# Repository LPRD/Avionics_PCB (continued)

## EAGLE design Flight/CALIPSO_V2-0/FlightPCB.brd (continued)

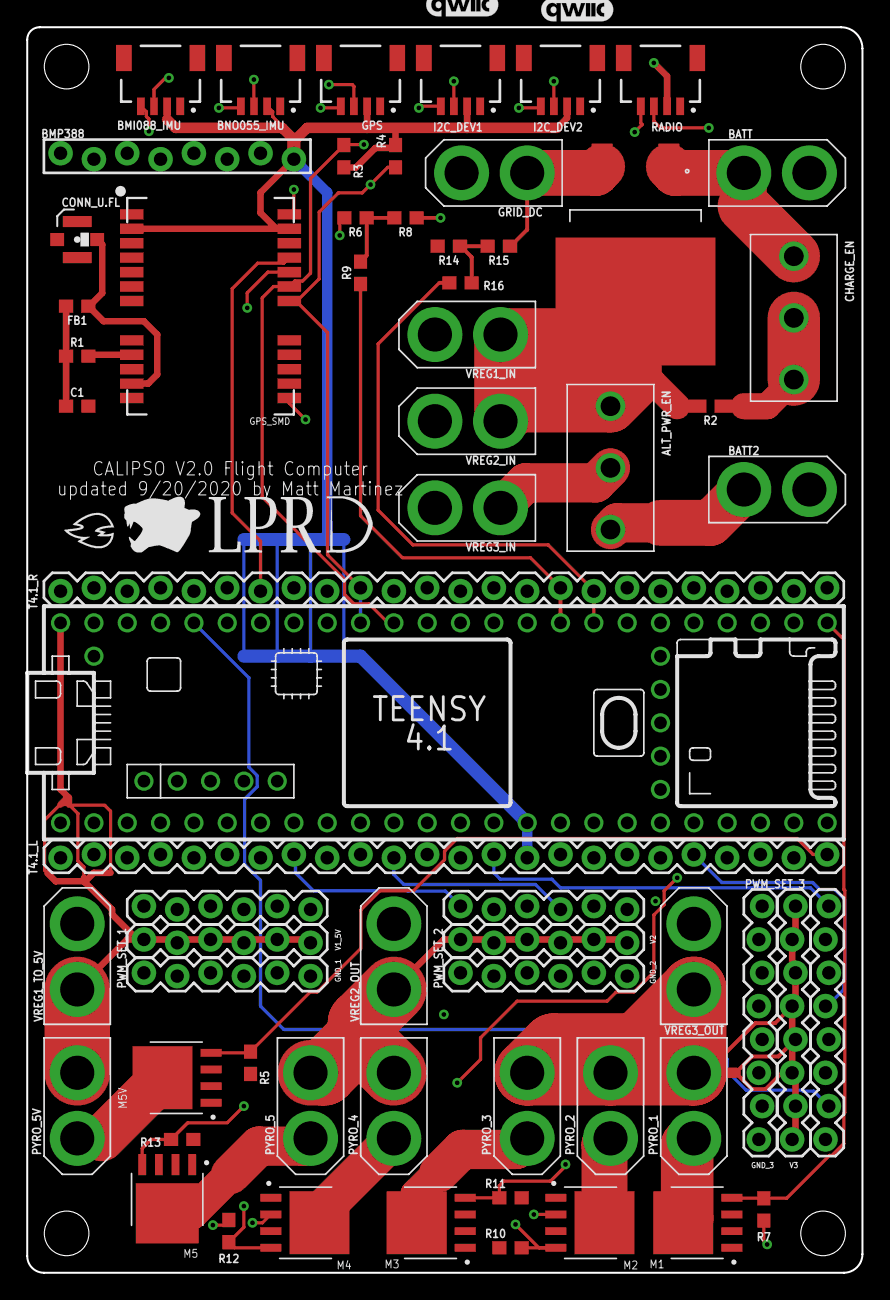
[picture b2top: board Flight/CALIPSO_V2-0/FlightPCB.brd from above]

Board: 4 copper layers, 63.6 x 94.9 mm, 65 parts (0 on the bottom side), 65 nets.

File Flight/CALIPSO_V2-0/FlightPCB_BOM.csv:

Part,Value,Device,Package,Description,PROD_ID,SF_ID,VALUE
ALT_PWR_EN,B2-Off-B1,CONN_03_SLIDE_SWITCH_EG5137,1X03_SLIDE_SWITCH_EG5137,Multi connection point. Often used as Generic Header-pin footprint for 0.1 inch spaced/style header connections,,,
BATT,XT-30,CONN_02_XT-30_CONNECTOR1X02_XT-30,1X02_BIG_XT-30,Multi connection point. Often used as Generic Header-pin footprint for 0.1 inch spaced/style header connections,,,
BATT2,XT-30,CONN_02_XT-30_CONNECTOR1X02_XT-30,1X02_BIG_XT-30,Multi connection point. Often used as Generic Header-pin footprint for 0.1 inch spaced/style header connections,,,
BMI088_IMU,QWIIC_RIGHT_ANGLE,QWIIC_CONNECTORJS-1MM,JST04_1MM_RA,SparkFun I2C Standard Qwiic Connector,CONN-13694,,QWIIC_RIGHT_ANGLE
BMP388,Pressure Sensor,CONN_08_BMP388_MODIFIEDFEMALE_LOCK,1X08_FEMALE_LOCK,Multi connection point. Often used as Generic Header-pin footprint for 0.1 inch spaced/style header connections,CONN-09233,PRT-09279,
BNO055_IMU,QWIIC_RIGHT_ANGLE,QWIIC_CONNECTORJS-1MM,JST04_1MM_RA,SparkFun I2C Standard Qwiic Connector,CONN-13694,,QWIIC_RIGHT_ANGLE
C1,47pF,47PF-0603-50V-5%,603,47pF ceramic capacitors,CAP-08913,,47pF
CHARGE_EN,Off-Off-Chg,CONN_03_SLIDE_SWITCH_EG5137,1X03_SLIDE_SWITCH_EG5137,Multi connection point. Often used as Generic Header-pin footprint for 0.1 inch spaced/style header connections,,,
CONN_U.FL,U.FL,U.FL2PIN,U.FL,SMD Antenna Connector - U.FL,CONN-09193,WRL-09144,U.FL
FB1,30Ω/1.8A,FERRITE_BEAD-0603,603,Ferrite Bead (blocks,,,
GND_1,6pin,CONN_06LOCK,1X06_LOCK,Multi connection point. Often used as Generic Header-pin footprint for 0.1 inch spaced/style header connections,,,
GND_2,6pin,CONN_06LOCK,1X06_LOCK,Multi connection point. Often used as Generic Header-pin footprint for 0.1 inch spaced/style header connections,,,
GND_3,8pin,CONN_08LOCK,1X08_LOCK,Multi connection point. Often used as Generic Header-pin footprint for 0.1 inch spaced/style header connections,,,
GPS,QWIIC_RIGHT_ANGLE,QWIIC_CONNECTORJS-1MM,JST04_1MM_RA,SparkFun I2C Standard Qwiic Connector,CONN-13694,,QWIIC_RIGHT_ANGLE
GPS_SMD,U-BLOX_NEO-M9N,U-BLOX_NEO-M9N,NEO-M9N/M8T/M8U,u-blox NEO-M9N GPS Module,IC-14651,,
GRID_DC,XT-30,CONN_02_XT-30_CONNECTOR1X02_XT-30,1X02_BIG_XT-30,Multi connection point. Often used as Generic Header-pin footprint for 0.1 inch spaced/style header connections,,,
I2C_DEV1,QWIIC_RIGHT_ANGLE,QWIIC_CONNECTORJS-1MM,JST04_1MM_RA,SparkFun I2C Standard Qwiic Connector,CONN-13694,,QWIIC_RIGHT_ANGLE
I2C_DEV2,QWIIC_RIGHT_ANGLE,QWIIC_CONNECTORJS-1MM,JST04_1MM_RA,SparkFun I2C Standard Qwiic Connector,CONN-13694,,QWIIC_RIGHT_ANGLE
LOGO1,QWIIC_LOGO_4MM,QWIIC_LOGO_4MM,QWIIC_4MM,Qwiic Logos for placement on schematic and PCB. The 5.5mm silk logo is best for placing next to Qwiic connector.,,,
LOGO2,QWIIC_LOGO_4MM,QWIIC_LOGO_4MM,QWIIC_4MM,Qwiic Logos for placement on schematic and PCB. The 5.5mm silk logo is best for placing next to Qwiic connector.,,,
M1,MOSFET_60V_22A,"BUK9Y43-60E,115",SOT-669-4,,,,
M2,MOSFET_60V_22A,"BUK9Y43-60E,115",SOT-669-4,,,,
M3,MOSFET_60V_22A,"BUK9Y43-60E,115",SOT-669-4,,,,
M4,MOSFET_60V_22A,"BUK9Y43-60E,115",SOT-669-4,,,,
M5,MOSFET_60V_22A,"BUK9Y43-60E,115",SOT-669-4,,,,
M5V,MOSFET_60V_22A,"BUK9Y43-60E,115",SOT-669-4,,,,
PWM_SET_1,6pin,CONN_06LOCK,1X06_LOCK,Multi connection point. Often used as Generic Header-pin footprint for 0.1 inch spaced/style header connections,,,
PWM_SET_2,6pin,CONN_06LOCK,1X06_LOCK,Multi connection point. Often used as Generic Header-pin footprint for 0.1 inch spaced/style header connections,,,
PWM_SET_3,8pin,CONN_08LOCK,1X08_LOCK,Multi connection point. Often used as Generic Header-pin footprint for 0.1 inch spaced/style header connections,,,
PWR_SWITCHER,STPS30170CG-TR_2_DIODES,STPS30170CG-TR,TO-263-3,,,,
PYRO_1,XT-30,CONN_02_XT-30_CONNECTOR1X02_XT-30,1X02_BIG_XT-30,Multi connection point. Often used as Generic Header-pin footprint for 0.1 inch spaced/style header connections,,,
PYRO_2,XT-30,CONN_02_XT-30_CONNECTOR1X02_XT-30,1X02_BIG_XT-30,Multi connection point. Often used as Generic Header-pin footprint for 0.1 inch spaced/style header connections,,,
PYRO_3,XT-30,CONN_02_XT-30_CONNECTOR1X02_XT-30,1X02_BIG_XT-30,Multi connection point. Often used as Generic Header-pin footprint for 0.1 inch spaced/style header connections,,,
PYRO_4,XT-30,CONN_02_XT-30_CONNECTOR1X02_XT-30,1X02_BIG_XT-30,Multi connection point. Often used as Generic Header-pin footprint for 0.1 inch spaced/style header connections,,,
PYRO_5,XT-30,CONN_02_XT-30_CONNECTOR1X02_XT-30,1X02_BIG_XT-30,Multi connection point. Often used as Generic Header-pin footprint for 0.1 inch spaced/style header connections,,,
PYRO_5V,XT-30,CONN_02_XT-30_CONNECTOR1X02_XT-30,1X02_BIG_XT-30,Multi connection point. Often used as Generic Header-pin footprint for 0.1 inch spaced/style header connections,,,
R1,10,10OHM-0603-1/10W-1%,603,10Ω resistor,RES-12581,,10
R2,1k,1KOHM-0603-1/10W-1%,603,1kΩ resistor,RES-07856,,1k
R3,4.7k,4.7KOHM-0603-1/10W-1%,603,4.7kΩ resistor,RES-07857,,4.7k
R4,4.7k,4.7KOHM-0603-1/10W-1%,603,4.7kΩ resistor,RES-07857,,4.7k
R5,10k,10KOHM-0603-1/10W-1%,603,10kΩ resistor,RES-00824,,10k
R6,1k,1KOHM-0603-1/10W-1%,603,1kΩ resistor,RES-07856,,1k
R7,10k,10KOHM-0603-1/10W-1%,603,10kΩ resistor,RES-00824,,10k
R8,20k,20KOHM-0603-1/10W-1%,603,20kΩ resistor,RES-09383,,20k
R9,20k,20KOHM-0603-1/10W-1%,603,20kΩ resistor,RES-09383,,20k
R10,10k,10KOHM-0603-1/10W-1%,603,10kΩ resistor,RES-00824,,10k
R11,10k,10KOHM-0603-1/10W-1%,603,10kΩ resistor,RES-00824,,10k
R12,10k,10KOHM-0603-1/10W-1%,603,10kΩ resistor,RES-00824,,10k
R13,10k,10KOHM-0603-1/10W-1%,603,10kΩ resistor,RES-00824,,10k
R14,1k,1KOHM-0603-1/10W-1%,603,1kΩ resistor,RES-07856,,1k
R15,20k,20KOHM-0603-1/10W-1%,603,20kΩ resistor,RES-09383,,20k
R16,20k,20KOHM-0603-1/10W-1%,603,20kΩ resistor,RES-09383,,20k
RADIO,QWIIC_RIGHT_ANGLE,QWIIC_CONNECTOR_SERIAL_RADIO_MODIFIEDJS-1MM,JST04_1MM_RA,SparkFun I2C Standard Qwiic Connector,CONN-13694,,QWIIC_RIGHT_ANGLE
T4.1_L,24p,CONN_24LOCK,1X24_LOCK,Multi connection point. Often used as Generic Header-pin footprint for 0.1 inch spaced/style header connections,,,
T4.1_R,24p,CONN_24LOCK,1X24_LOCK,Multi connection point. Often used as Generic Header-pin footprint for 0.1 inch spaced/style header connections,,,
TEENSY_4.1,TEENSY_4.1,TEENSY_4.1,TEENSY_4.1,,,,
V1_5V,6 pin,CONN_06LOCK,1X06_LOCK,Multi connection point. Often used as Generic Header-pin footprint for 0.1 inch spaced/style header connections,,,
V2,6 pin,CONN_06LOCK,1X06_LOCK,Multi connection point. Often used as Generic Header-pin footprint for 0.1 inch spaced/style header connections,,,
V3,8 pin,CONN_08LOCK,1X08_LOCK,Multi connection point. Often used as Generic Header-pin footprint for 0.1 inch spaced/style header connections,,,
VREG1_IN,XT-30,CONN_02_XT-30_CONNECTOR1X02_XT-30,1X02_BIG_XT-30,Multi connection point. Often used as Generic Header-pin footprint for 0.1 inch spaced/style header connections,,,
VREG1_TO_5V,XT-30,CONN_02_XT-30_CONNECTOR1X02_XT-30,1X02_BIG_XT-30,Multi connection point. Often used as Generic Header-pin footprint for 0.1 inch spaced/style header connections,,,
VREG2_IN,XT-30,CONN_02_XT-30_CONNECTOR1X02_XT-30,1X02_BIG_XT-30,Multi connection point. Often used as Generic Header-pin footprint for 0.1 inch spaced/style header connections,,,
VREG2_OUT,XT-30,CONN_02_XT-30_CONNECTOR1X02_XT-30,1X02_BIG_XT-30,Multi connection point. Often used as Generic Header-pin footprint for 0.1 inch spaced/style header connections,,,
VREG3_IN,XT-30,CONN_02_XT-30_CONNECTOR1X02_XT-30,1X02_BIG_XT-30,Multi connection point. Often used as Generic Header-pin footprint for 0.1 inch spaced/style header connections,,,
VREG3_OUT,XT-30,CONN_02_XT-30_CONNECTOR1X02_XT-30,1X02_BIG_XT-30,Multi connection point. Often used as Generic Header-pin footprint for 0.1 inch spaced/style header connections,,,

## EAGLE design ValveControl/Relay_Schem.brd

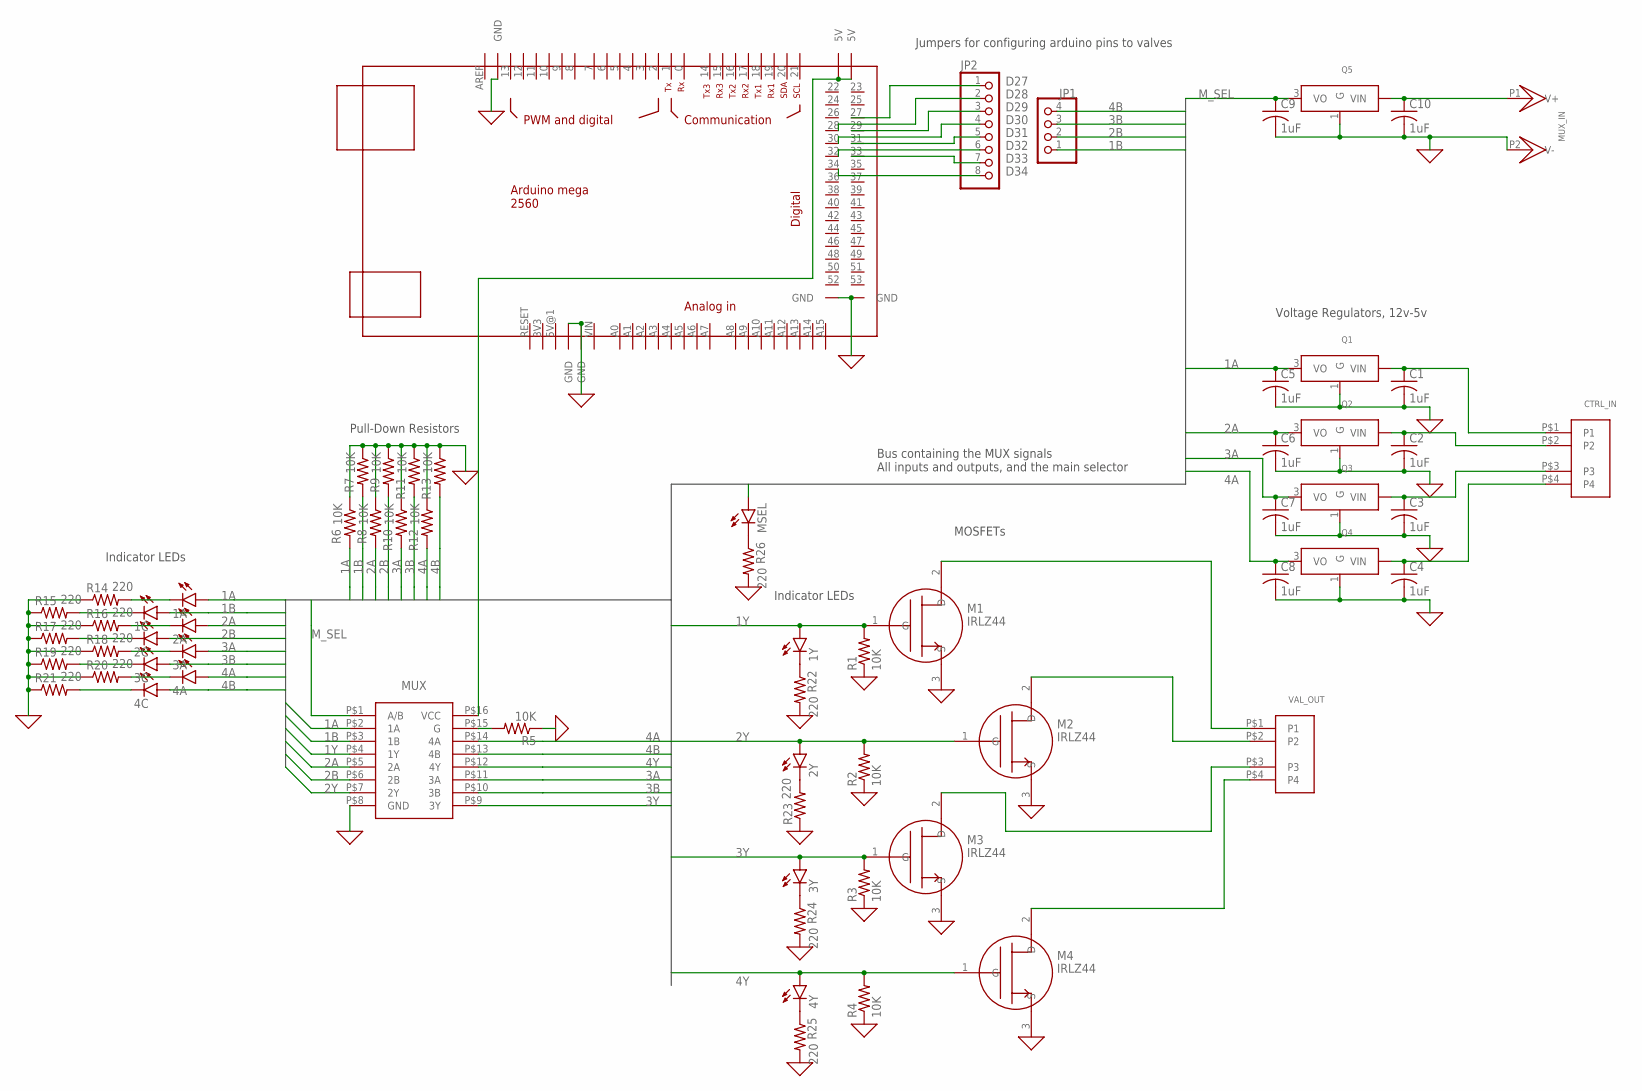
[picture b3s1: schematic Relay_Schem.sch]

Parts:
1A, 1C, 1Y, 2A, 2C, 2Y, 3A, 3C, 3Y, 4A, 4C, 4Y: LED3MM
C1, C2, C3, C4, C5, C6, C7, C8, C9, C10: 1uF; C025-024X044
CTRL_IN: JST_CONNECTOR; B4B-XH-A(LF)(SN)
JP1: PINHD-1X4; 1X04
JP2: PINHD-1X8; 1X08
M1, M2, M3, M4: IRLZ44; TO220V
MSEL: LED3MM
MUX: MULTIPLEXER; SN74HC157
MUX_IN: COAX_POW_2.1MM; PJ-102A
Q1, Q2, Q3, Q4, Q5: LINEAR_REGULATOR; LINREG_FP
R1, R2, R3, R4, R5, R6, R7, R8, R9, R10, R11, R12, R13: 10K; 0204/7
R14, R15, R16, R17, R18, R19, R20, R21, R22, R23, R24, R25, R26: 220; 0204/7
U$2: MEGA_DEVICE; MEGAOUTLINE
VAL_OUT: JST_CONNECTOR; B4B-XH-A(LF)(SN)

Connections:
0: C1.2, C2.2, C3.2, C4.2, C5.2, C6.2, C7.2, C8.2, C9.2, C10.2, M1.3 (S), M2.3 (S), M3.3 (S), M4.3 (S), MUX.P$8 (GND), MUX_IN.P2 (V-), Q1.1 (G), Q2.1 (G), Q3.1 (G), Q4.1 (G), Q5.1 (G), R1.1, R2.1, R3.1, R4.1, R5.1, R6.1, R7.1, R8.1, R9.1, R10.1, R11.1, R12.1, R13.1, R14.1, R15.1, R16.1, R17.1, R18.1, R19.1, R20.1, R21.1, R22.2, R23.1, R24.2, R25.2, R26.2, U$2.GND@1 (GND), U$2.GND@2 (GND), U$2.GND@3 (GND), U$2.GND@4 (GND), U$2.GND@5 (GND)
1A: 1A.A, C5.1, MUX.P$2 (1A), Q1.3 (VO), R6.2
1B: 1C.A, JP1.1, MUX.P$3 (1B), R7.2
1Y: 1Y.A, M1.1 (G), MUX.P$4 (1Y), R1.2
2A: 2A.A, C6.1, MUX.P$5 (2A), Q2.3 (VO), R8.2
2B: 2C.A, JP1.2, MUX.P$6 (2B), R9.2
2Y: 2Y.A, M2.1 (G), MUX.P$7 (2Y), R2.2
3A: 3A.A, C7.1, MUX.P$11 (3A), Q3.3 (VO), R10.2
3B: 3C.A, JP1.3, MUX.P$10 (3B), R11.2
3Y: 3Y.A, M3.1 (G), MUX.P$9 (3Y), R3.2
4A: 4A.A, C8.1, MUX.P$14 (4A), Q4.3 (VO), R12.2
4B: 4C.A, JP1.4, MUX.P$13 (4B), R13.2
4Y: 4Y.A, M4.1 (G), MUX.P$12 (4Y), R4.2
D27: JP2.1, U$2.27
D28: JP2.2, U$2.28
D29: JP2.3, U$2.29
D30: JP2.4, U$2.30
D31: JP2.5, U$2.31
D32: JP2.6, U$2.32
D33: JP2.7, U$2.33
D34: JP2.8, U$2.34
M_SEL: C9.1, MSEL.A, MUX.P$1 (A/B), Q5.3 (VO)
unnamed: C1.1, CTRL_IN.P$1 (P1), Q1.2 (VIN)
unnamed: C2.1, CTRL_IN.P$2 (P2), Q2.2 (VIN)
unnamed: M1.2 (D), VAL_OUT.P$1 (P1)
unnamed: C3.1, CTRL_IN.P$3 (P3), Q3.2 (VIN)
unnamed: M2.2 (D), VAL_OUT.P$2 (P2)
unnamed: MUX.P$16 (VCC), U$2.5V@2 (5V), U$2.5V@3 (5V)
unnamed: MSEL.K (C), R26.1
unnamed: M3.2 (D), VAL_OUT.P$3 (P3)
unnamed: M4.2 (D), VAL_OUT.P$4 (P4)
unnamed: MUX.P$15 (G), R5.2
unnamed: 1Y.K (C), R22.1
unnamed: C4.1, CTRL_IN.P$4 (P4), Q4.2 (VIN)
unnamed: 4A.K (C), R20.2
unnamed: 3A.K (C), R18.2
unnamed: 2A.K (C), R16.2
unnamed: 1A.K (C), R14.2
unnamed: 1C.K (C), R15.2
unnamed: 2C.K (C), R17.2
unnamed: 3C.K (C), R19.2
unnamed: 4C.K (C), R21.2
unnamed: 2Y.K (C), R23.2
unnamed: 3Y.K (C), R24.1
unnamed: 4Y.K (C), R25.1
unnamed: C10.1, MUX_IN.P1 (V+), Q5.2 (VIN)

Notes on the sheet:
MOSFETs
Indicator LEDs
Pull-Down Resistors
Voltage Regulators, 12v-5v
Bus containing the MUX signals All inputs and outputs, and the main selector
Jumpers for configuring arduino pins to valves

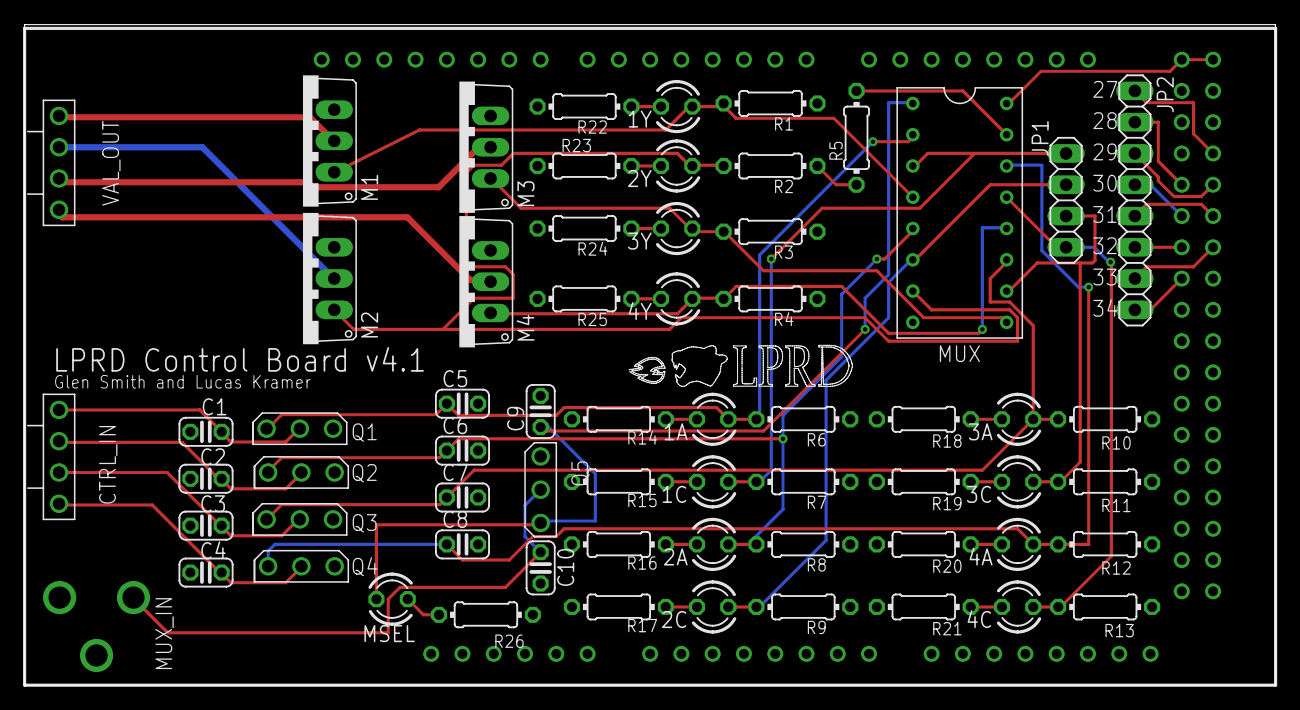
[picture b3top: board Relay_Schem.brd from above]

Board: 2 copper layers, 101.6 x 53.6 mm, 65 parts (0 on the bottom side), 46 nets.

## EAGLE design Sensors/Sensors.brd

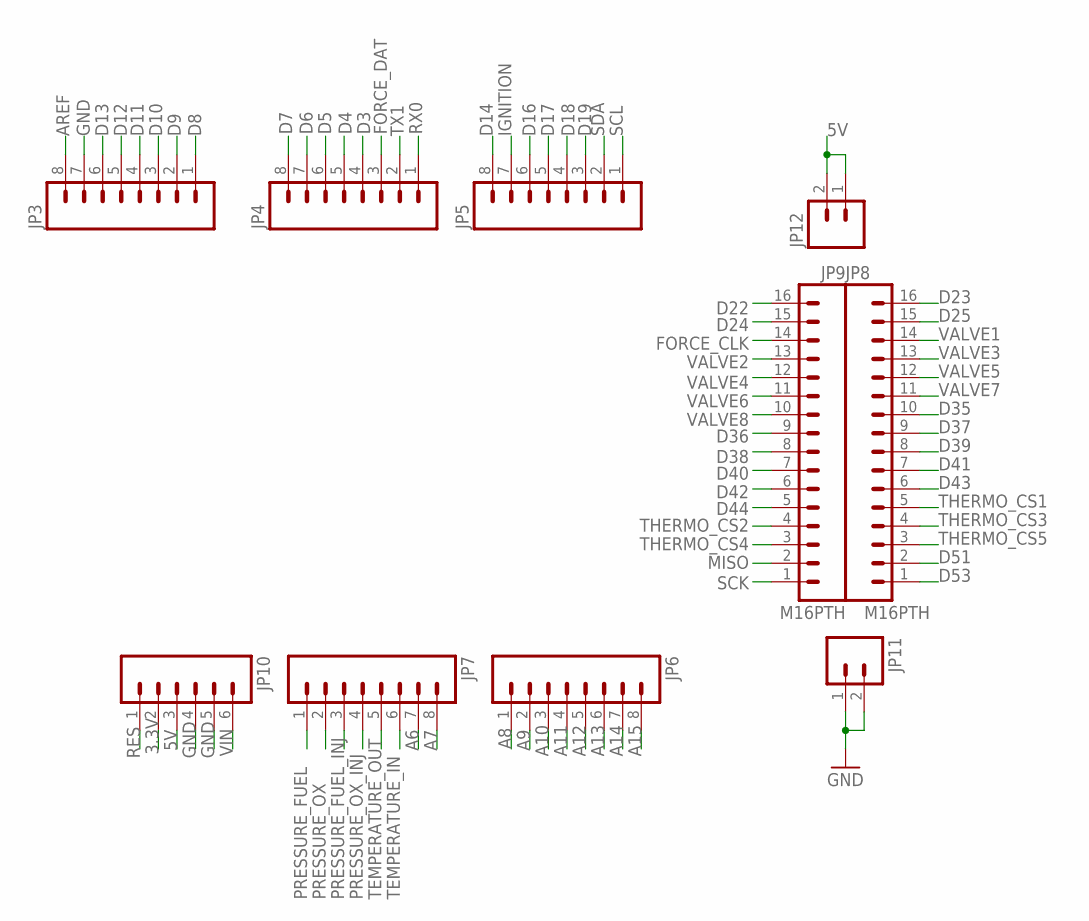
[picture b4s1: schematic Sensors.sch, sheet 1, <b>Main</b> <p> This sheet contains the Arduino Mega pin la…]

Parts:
JP3, JP4, JP5, JP6, JP7: M08; 1X08
JP8, JP9: M16PTH; 1X16
JP10: M06SIP; 1X06
JP11, JP12: M02PTH; 1X02

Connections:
3.3V: JP10.2
5V: JP10.3, JP12.1, JP12.2; also elsewhere on the board
A6: JP7.7
A7: JP7.8
A8: JP6.1
A9: JP6.2
A10: JP6.3
A11: JP6.4
A12: JP6.5
A13: JP6.6
A14: JP6.7
A15: JP6.8
AREF: JP3.8
D3: JP4.4
D4: JP4.5
D5: JP4.6
D6: JP4.7
D7: JP4.8
D8: JP3.1
D9: JP3.2
D10: JP3.3
D11: JP3.4
D12: JP3.5
D13: JP3.6
D14: JP5.8
D16: JP5.6
D17: JP5.5
D18: JP5.4
D19: JP5.3
D22: JP9.16
D23: JP8.16
D24: JP9.15
D25: JP8.15
D35: JP8.10
D36: JP9.9
D37: JP8.9
D38: JP9.8
D39: JP8.8
D40: JP9.7
D41: JP8.7
D42: JP9.6
D43: JP8.6
D44: JP9.5
D51: JP8.2
D53: JP8.1
FORCE_CLK: JP9.14; also elsewhere on the board
FORCE_DAT: JP4.3; also elsewhere on the board
GND: JP3.7, JP10.4, JP10.5, JP11.1, JP11.2; also elsewhere on the board
IGNITION: JP5.7
MISO: JP9.2; also elsewhere on the board
PRESSURE_FUEL: JP7.1; also elsewhere on the board
PRESSURE_FUEL_INJ: JP7.3; also elsewhere on the board
PRESSURE_OX: JP7.2; also elsewhere on the board
PRESSURE_OX_INJ: JP7.4; also elsewhere on the board
RES: JP10.1
RX0: JP4.1
SCK: JP9.1; also elsewhere on the board
SCL: JP5.1; also elsewhere on the board
SDA: JP5.2; also elsewhere on the board
TEMPERATURE_IN: JP7.6; also elsewhere on the board
TEMPERATURE_OUT: JP7.5; also elsewhere on the board
THERMO_CS1: JP8.5; also elsewhere on the board
THERMO_CS2: JP9.4; also elsewhere on the board
THERMO_CS3: JP8.4; also elsewhere on the board
THERMO_CS4: JP9.3; also elsewhere on the board
THERMO_CS5: JP8.3; also elsewhere on the board
TX1: JP4.2
VALVE1: JP8.14
VALVE2: JP9.13
VALVE3: JP8.13
VALVE4: JP9.12
VALVE5: JP8.12
VALVE6: JP9.11
VALVE7: JP8.11
VALVE8: JP9.10
VIN: JP10.6

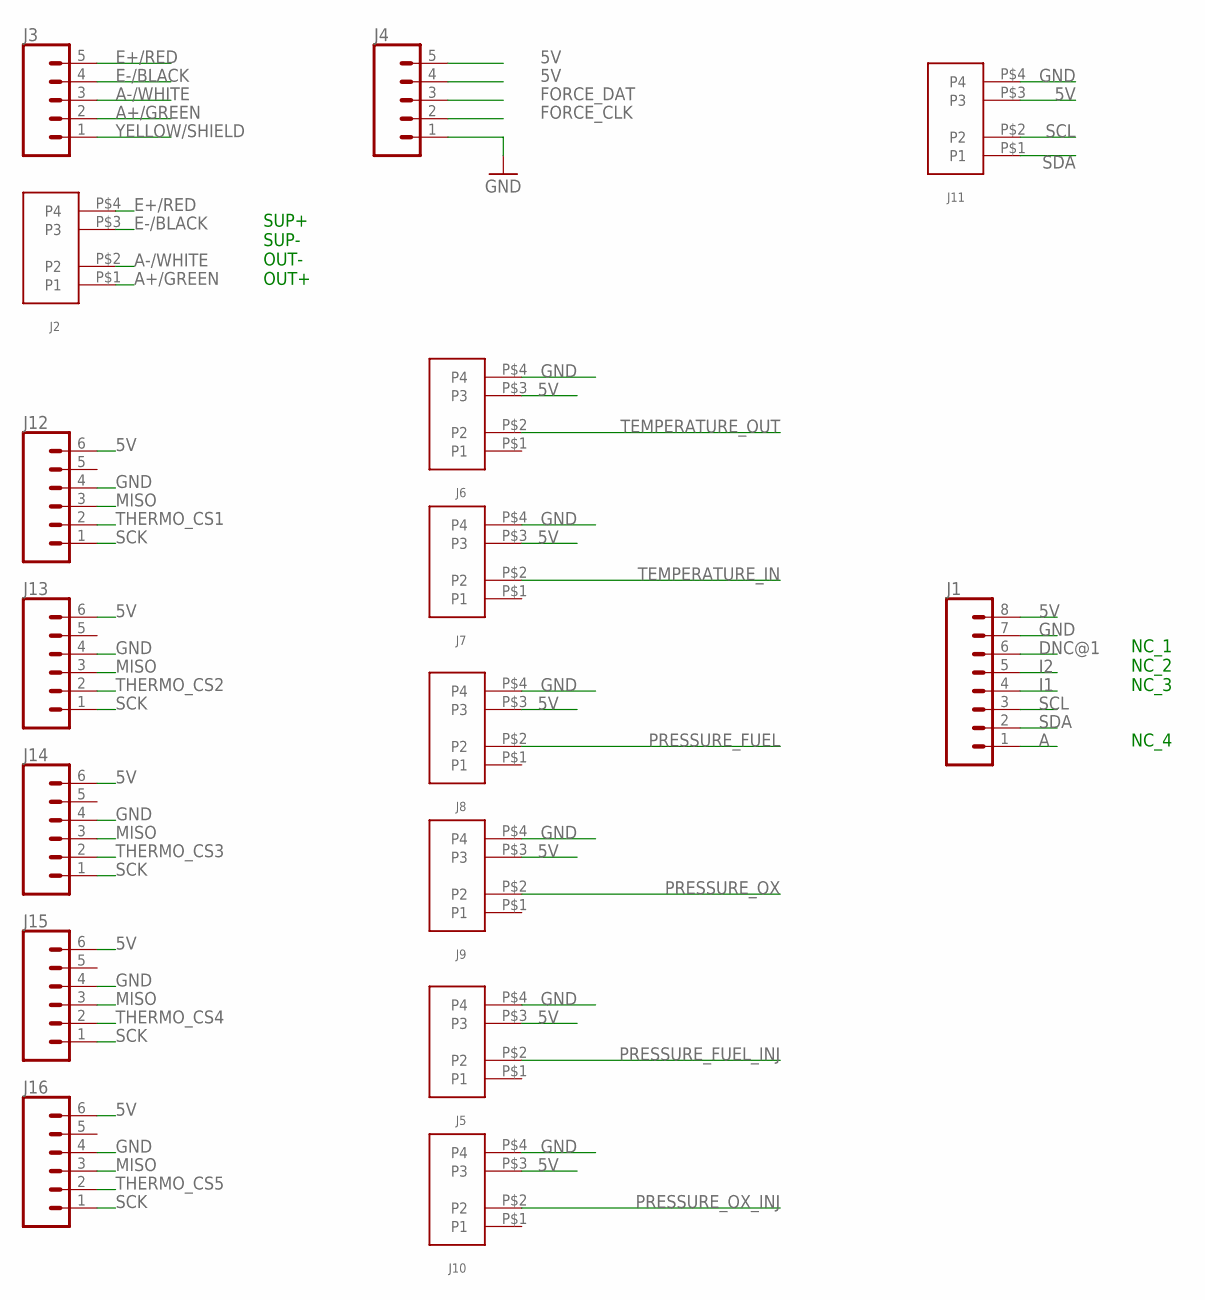
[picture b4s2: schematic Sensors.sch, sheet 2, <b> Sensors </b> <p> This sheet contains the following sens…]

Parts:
J1: CONN_08"; 1X08
J2, J5, J6, J7, J8, J9, J10, J11: JST_CONNECTOR; B4B-XH-A(LF)(SN)
J3, J4: CONN_05; 1X05
J12, J13, J14, J15, J16: CONN_06SILK_FEMALE_PTH; 1X06

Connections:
5V: J1.8, J4.4, J4.5, J5.P$3 (P3), J6.P$3 (P3), J7.P$3 (P3), J8.P$3 (P3), J9.P$3 (P3), J10.P$3 (P3), J11.P$3 (P3), J12.6, J13.6, J14.6, J15.6, J16.6; also elsewhere on the board
A: J1.1
A+/GREEN: J2.P$1 (P1), J3.2
A-/WHITE: J2.P$2 (P2), J3.3
DNC@1: J1.6
E+/RED: J2.P$4 (P4), J3.5
E-/BLACK: J2.P$3 (P3), J3.4
FORCE_CLK: J4.2; also elsewhere on the board
FORCE_DAT: J4.3; also elsewhere on the board
GND: J1.7, J4.1, J5.P$4 (P4), J6.P$4 (P4), J7.P$4 (P4), J8.P$4 (P4), J9.P$4 (P4), J10.P$4 (P4), J11.P$4 (P4), J12.4, J13.4, J14.4, J15.4, J16.4; also elsewhere on the board
I1: J1.4
I2: J1.5
MISO: J12.3, J13.3, J14.3, J15.3, J16.3; also elsewhere on the board
PRESSURE_FUEL: J8.P$2 (P2); also elsewhere on the board
PRESSURE_FUEL_INJ: J5.P$2 (P2); also elsewhere on the board
PRESSURE_OX: J9.P$2 (P2); also elsewhere on the board
PRESSURE_OX_INJ: J10.P$2 (P2); also elsewhere on the board
SCK: J12.1, J13.1, J14.1, J15.1, J16.1; also elsewhere on the board
SCL: J1.3, J11.P$2 (P2); also elsewhere on the board
SDA: J1.2, J11.P$1 (P1); also elsewhere on the board
TEMPERATURE_IN: J7.P$2 (P2); also elsewhere on the board
TEMPERATURE_OUT: J6.P$2 (P2); also elsewhere on the board
THERMO_CS1: J12.2; also elsewhere on the board
THERMO_CS2: J13.2; also elsewhere on the board
THERMO_CS3: J14.2; also elsewhere on the board
THERMO_CS4: J15.2; also elsewhere on the board
THERMO_CS5: J16.2; also elsewhere on the board
YELLOW/SHIELD: J3.1

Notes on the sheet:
SUP+ SUP- OUT- OUT+
NC_1 NC_2 NC_3
NC_4

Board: 2 copper layers, 28 parts (0 on the bottom side), 23 nets, no tracks yet.

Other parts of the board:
T$1: UMNLOGO
U$2: LPRDLOGO

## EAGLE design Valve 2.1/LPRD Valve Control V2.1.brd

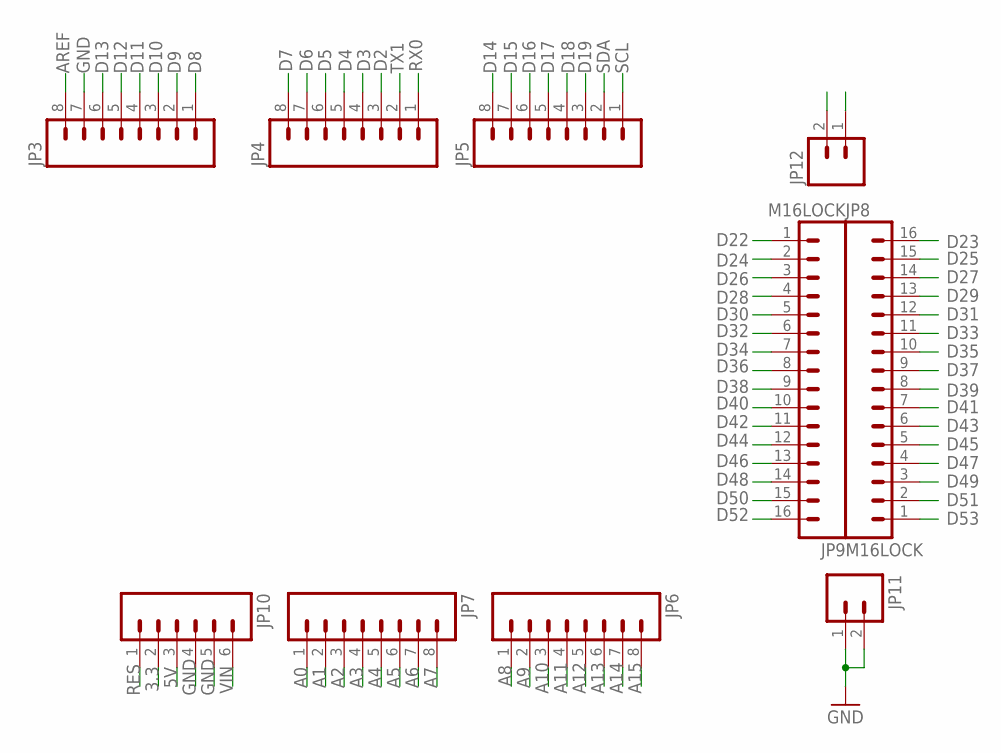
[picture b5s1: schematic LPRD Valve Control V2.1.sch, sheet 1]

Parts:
JP3, JP4, JP5, JP6, JP7: M08LOCK; 1X08_LOCK
JP8, JP9: M16LOCK; 1X16_LOCK
JP10: M06LOCK; 1X06_LOCK
JP11, JP12: M02LOCK; 1X02_LOCK

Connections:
3.3: JP10.2
5V: JP10.3
5V@1: JP12.1, JP12.2; also elsewhere on the board
A0: JP7.1
A1: JP7.2
A2: JP7.3
A3: JP7.4
A4: JP7.5
A5: JP7.6
A6: JP7.7
A7: JP7.8
A8: JP6.1
A9: JP6.2
A10: JP6.3
A11: JP6.4
A12: JP6.5
A13: JP6.6
A14: JP6.7
A15: JP6.8
AREF: JP3.8
D2: JP4.3
D3: JP4.4
D4: JP4.5
D5: JP4.6
D6: JP4.7
D7: JP4.8
D8: JP3.1
D9: JP3.2
D10: JP3.3
D11: JP3.4
D12: JP3.5
D13: JP3.6
D14: JP5.8
D15: JP5.7
D16: JP5.6
D17: JP5.5
D18: JP5.4
D19: JP5.3
D22: JP9.1
D23: JP8.16
D24: JP9.2
D25: JP8.15
D26: JP9.3
D27: JP8.14
D28: JP9.4
D29: JP8.13
D30: JP9.5
D31: JP8.12
D32: JP9.6
D33: JP8.11
D34: JP9.7
D35: JP8.10
D36: JP9.8
D37: JP8.9; also elsewhere on the board
D38: JP9.9; also elsewhere on the board
D39: JP8.8; also elsewhere on the board
D40: JP9.10; also elsewhere on the board
D41: JP8.7
D42: JP9.11
D43: JP8.6
D44: JP9.12
D45: JP8.5
D46: JP9.13
D47: JP8.4
D48: JP9.14
D49: JP8.3
D50: JP9.15
D51: JP8.2
D52: JP9.16
D53: JP8.1
GND: JP3.7, JP10.4, JP10.5, JP11.1, JP11.2; also elsewhere on the board
RES: JP10.1
RX0: JP4.1
SCL: JP5.1
SDA: JP5.2
TX1: JP4.2
VIN: JP10.6

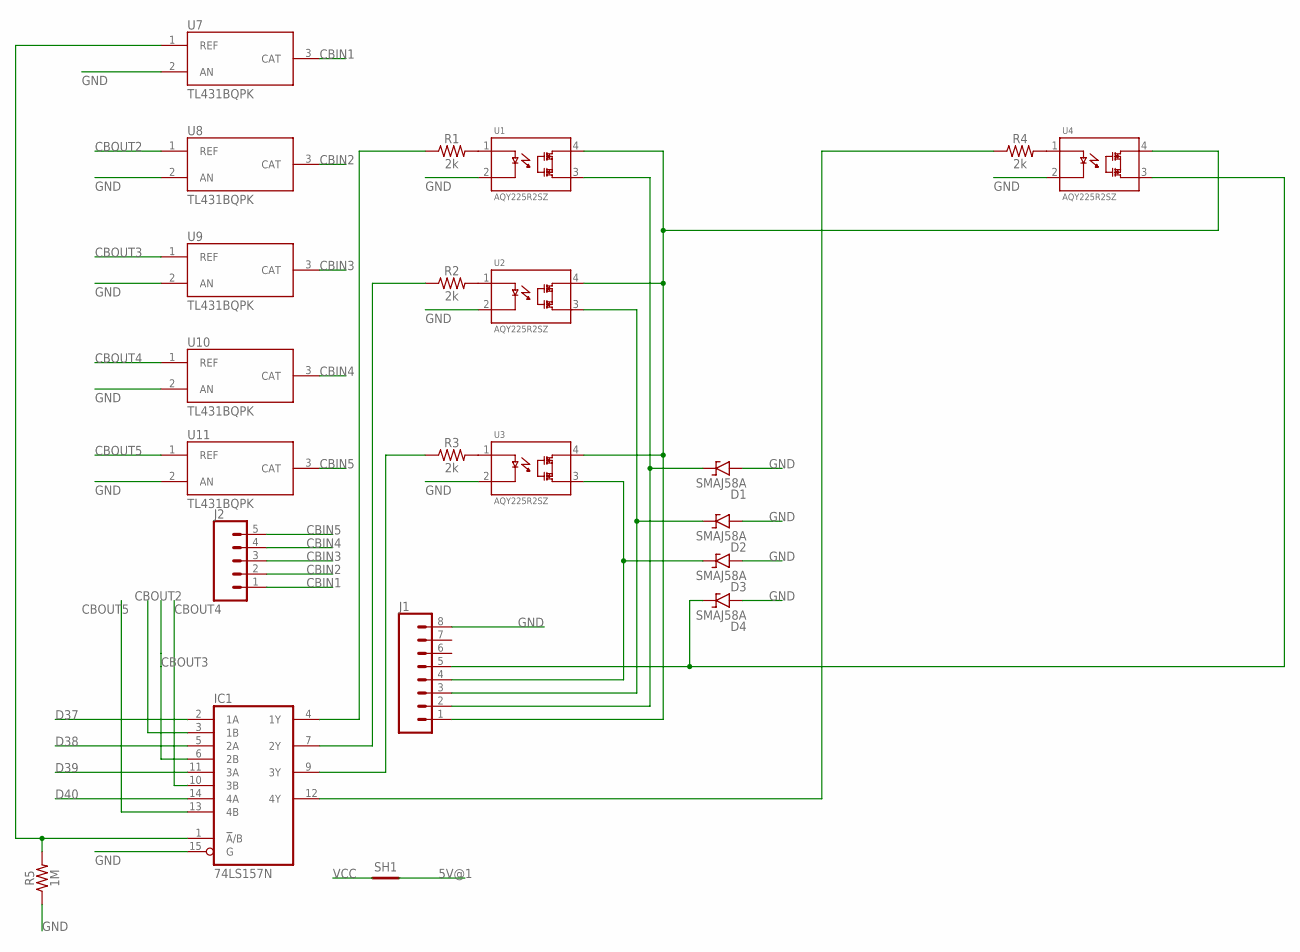
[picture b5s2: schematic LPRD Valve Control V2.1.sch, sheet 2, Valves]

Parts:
D1, D2, D3, D4: SMAJ58A; SMA
IC1: 74LS157N; DIL16
J1: CONN_08"; 1X08
J2: CONN_05; 1X05
R1, R2, R3, R4: 2k; 0805
R5: 1M; 0805
SH1: SHORTT5; SHORT_TOP-50
U1, U2, U3, U4: AQY225R2SZ; SOIC254P680X220-4N
U7, U8, U9, U10, U11: TL431BQPK; VREG_TL431BQPK

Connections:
5V@1: SH1.2; also elsewhere on the board
CBIN1: J2.1, U7.3 (CAT)
CBIN2: J2.2, U8.3 (CAT)
CBIN3: J2.3, U9.3 (CAT)
CBIN4: J2.4, U10.3 (CAT)
CBIN5: J2.5, U11.3 (CAT)
CBOUT2: IC1.3 (1B), U8.1 (REF)
CBOUT3: IC1.6 (2B), U9.1 (REF)
CBOUT4: IC1.10 (3B), U10.1 (REF)
CBOUT5: IC1.13 (4B), U11.1 (REF)
D37: IC1.2 (1A); also elsewhere on the board
D38: IC1.5 (2A); also elsewhere on the board
D39: IC1.11 (3A); also elsewhere on the board
D40: IC1.14 (4A); also elsewhere on the board
GND: D1.A, D2.A, D3.A, D4.A, IC1.8 (GND), IC1.15 (G), J1.8, R5.1, U1.2, U2.2, U3.2, U4.2, U7.2 (AN), U8.2 (AN), U9.2 (AN), U10.2 (AN), U11.2 (AN); also elsewhere on the board
unnamed: R1.2, U1.1
unnamed: R2.2, U2.1
unnamed: R3.2, U3.1
unnamed: R4.2, U4.1
unnamed: J1.1, U1.4, U2.4, U3.4, U4.4
unnamed: D1.C, J1.2, U1.3
unnamed: D2.C, J1.3, U2.3
unnamed: D3.C, J1.4, U3.3
unnamed: D4.C, J1.5, U4.3
unnamed: IC1.4 (1Y), R1.1
unnamed: IC1.7 (2Y), R2.1
unnamed: IC1.9 (3Y), R3.1
unnamed: IC1.12 (4Y), R4.1
unnamed: IC1.1 (!A!/B), R5.2, U7.1 (REF)
VCC: IC1.16 (VCC), SH1.1

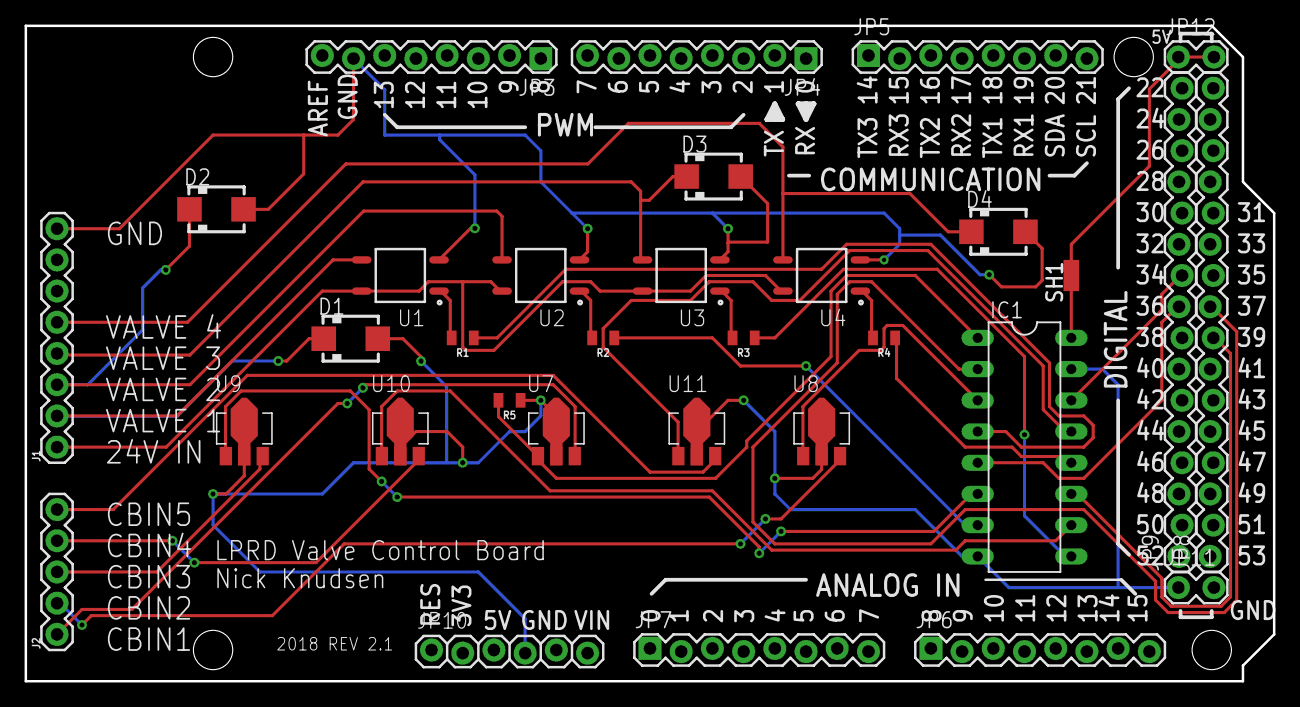
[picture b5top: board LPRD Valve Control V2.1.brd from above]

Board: 2 copper layers, 101.6 x 53.3 mm, 34 parts (0 on the bottom side), 30 nets.

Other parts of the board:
U$1: UMNLOGO
U$2: LPRDLOGO
